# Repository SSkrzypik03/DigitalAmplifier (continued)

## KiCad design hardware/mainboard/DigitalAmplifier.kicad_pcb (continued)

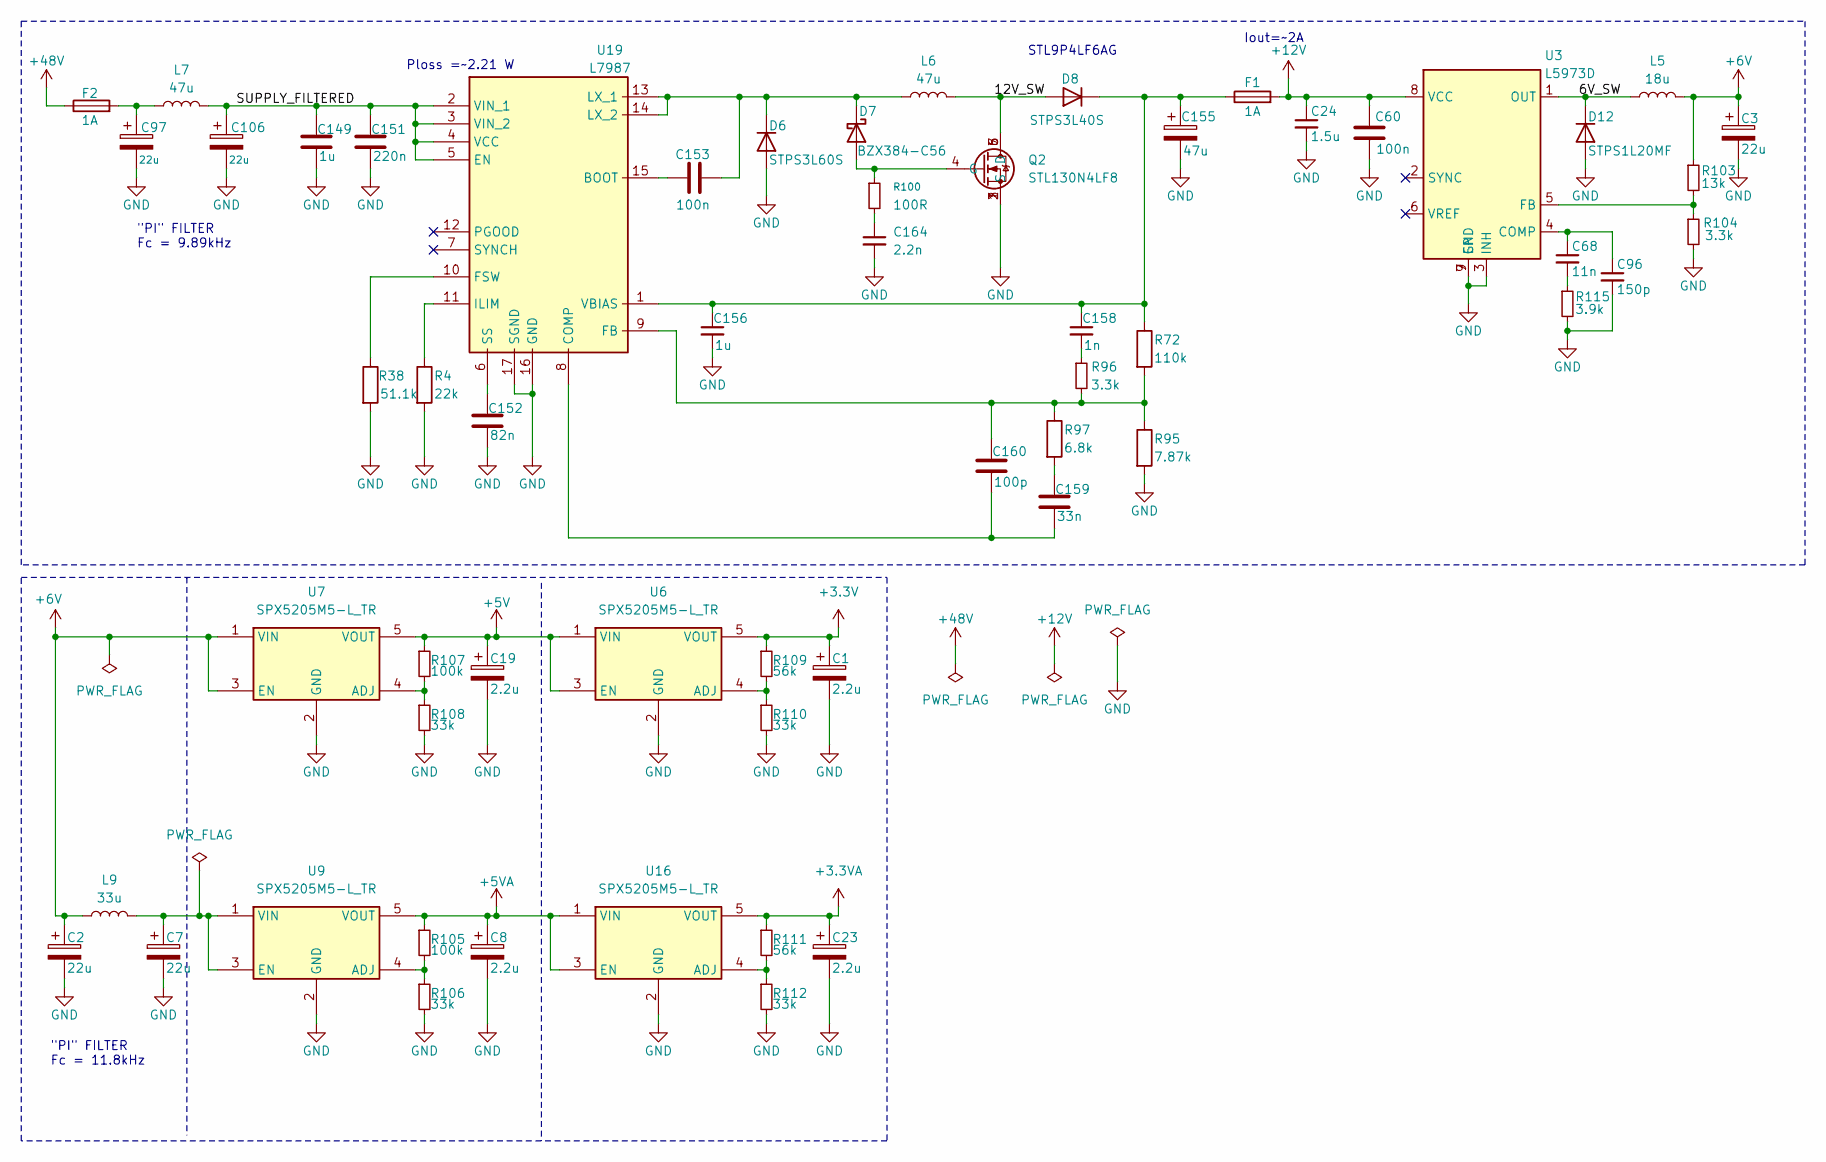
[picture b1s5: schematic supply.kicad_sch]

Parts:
C1, C8, C19, C23: 2.2u; CAPPM3216X180N; Manufacturer_Part_Number 293D225X9016A2TE3
C2, C3, C7: 22u; CAPPM3216X180N; Manufacturer_Part_Number 293D226X9010A2TE3
C24: 1.5u; C_0603_1608Metric; Manufacturer_Part_Number GRM155Z71A225KE01D
C60, C153: 100n; C_0603_1608Metric; Manufacturer_Part_Number 0603B104K500CT
C68: 11n; C_0603_1608Metric; Manufacturer_Part_Number GRM155Z71A225KE01D
C96: 150p; C_0603_1608Metric; Manufacturer_Part_Number GRM155Z71A225KE01D
C97, C106: 22u; CP_Radial_D4.0mm_P2.00mm; Manufacturer_Part_Number ECA1JHG220
C149, C156: 1u; C_0603_1608Metric; Manufacturer_Part_Number CL10A105KB8NNNC
C151: 220n; C_0603_1608Metric; Manufacturer_Part_Number CL10B224KO8NNNC
C152: 82n; C_0603_1608Metric; Manufacturer_Part_Number C0603C823K5RACTU
C155: 47u; CAPPM7343X310N; Manufacturer_Part_Number 293D476X9025D2TE3
C158: 1n; C_0603_1608Metric; Manufacturer_Part_Number 0603B102K500CT
C159: 33n; C_0603_1608Metric; Manufacturer_Part_Number CC0603JRX7R9BB333
C160: 100p; C_0603_1608Metric; Manufacturer_Part_Number CL10C101JB8NNNC
C164: 2.2n; C_0603_1608Metric; Manufacturer_Part_Number GRM1885C1H222JA01D
D6: STPS3L60S; D_SMC; Manufacturer_Part_Number STPS3L60S
D7: BZX384-C56; D_SOD-323; Manufacturer_Part_Number BZX384-C56
D8: STPS3L40S; D_SMC; Manufacturer_Part_Number STPS3L40S
D12: STPS1L20MF; Manufacturer_Part_Number STPS1L20MF
F1, F2: 1A; 0154001.DRT; Manufacturer_Part_Number 0154001.DRT
L5: 18u; L_Wurth_WE-PD2-1054; Manufacturer_Part_Number 744776118
L6: 47u; INDPM120120X1020N; Manufacturer_Part_Number MSS1210-473MED
L7: 47u; INDPM8180X540N; Manufacturer_Part_Number HCM1A0805V2-470-R
L9: 33u; WE-LQ_L49; Manufacturer_Part_Number 744045330
Q2: STL130N4LF8; STL9P4LF6AG; Manufacturer_Part_Number STL130N4LF8
R4: 22k; R_0603_1608Metric; Manufacturer_Part_Number WR06X2202FTL
R38: 51.1k; R_0603_1608Metric; Manufacturer_Part_Number ERJ3EKF5112V
R72: 110k; R_0603_1608Metric; Manufacturer_Part_Number ERJ3GEYJ114V
R95: 7.87k; R_0603_1608Metric; Manufacturer_Part_Number ERJ3EKF7871V
R96, R104: 3.3k; R_0603_1608Metric; Manufacturer_Part_Number ERA-2ARC2612X
R97: 6.8k; R_0603_1608Metric; Manufacturer_Part_Number RC0603FR-076K8L
R100: 100R; R_0603_1608Metric; Manufacturer_Part_Number WR06X1000FTL
R103: 13k; R_0603_1608Metric; Manufacturer_Part_Number RC0402BR-07220KL
R105, R107: 100k; R_0603_1608Metric; Manufacturer_Part_Number CRCW0402100KFKED
R106, R108, R110, R112: 33k; R_0603_1608Metric; Manufacturer_Part_Number ERA2AEB333X
R109, R111: 56k; R_0603_1608Metric; Manufacturer_Part_Number CR0402-FX-5602GLF
R115: 3.9k; R_0603_1608Metric; Manufacturer_Part_Number RC0402BR-07220KL
U3: L5973D; HSOP-8-1EP_3.9x4.9mm_P1.27mm_EP2.41x3.1mm_ThermalVias; Manufacturer_Part_Number L5973D013TR
U6, U7, U9, U16: SPX5205M5-L_TR; SOT95P280X145-5N; Mouser Part Number 701-SPX5205M5-L/TR
U19: L7987; SOP65P640X120-17N; Manufacturer_Part_Number L7987

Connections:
+3.3V: C1.1, R109.1, U6.5 (VOUT); also elsewhere on the board
+3.3VA: C23.1, R111.1, U16.5 (VOUT); also elsewhere on the board
+5V: C19.1, R107.1, U6.1 (VIN), U6.3 (EN), U7.5 (VOUT); also elsewhere on the board
+5VA: C8.1, R105.1, U9.5 (VOUT), U16.1 (VIN), U16.3 (EN); also elsewhere on the board
+6V: C2.1, C3.1, L5.2, L9.1, R103.1, U7.1 (VIN), U7.3 (EN)
+12V: C24.1, C60.2, F1.2, U3.8 (VCC); also elsewhere on the board
+48V: F2.1; also elsewhere on the board
/Supply/6V_SW: D12.2 (K), D12.3 (K), L5.1, U3.1 (OUT)
/Supply/12V_SW: D8.2 (A), L6.2, Q2.5 (D), Q2.6 (D), Q2.7 (D)
/Supply/SUPPLY_FILTERED: C106.1, C149.1, C151.1, L7.2, U19.2 (VIN_1), U19.3 (VIN_2), U19.4 (VCC), U19.5 (EN)
GND: C1.2, C2.2, C3.2, C7.2, C8.2, C19.2, C23.2, C24.2, C60.1, C96.2, C97.2, C106.2, C149.2, C151.2, C152.2, C155.2, C156.2, C164.2, D6.2 (A), D12.1 (A), Q2.1 (S), Q2.2 (S), Q2.3 (S), R4.2, R38.2, R95.2, R104.2, R106.2, R108.2, R110.2, R112.2, R115.2, U3.3 (INH), U3.7 (GND), U3.9 (EP), U6.2 (GND), U7.2 (GND), U9.2 (GND), U16.2 (GND), U19.16 (GND), U19.17 (SGND); also elsewhere on the board
unnamed: C68.2, R115.1
unnamed: C97.1, F2.2, L7.1
unnamed: C158.2, R96.1
unnamed: C159.1, R97.2
unnamed: C164.1, R100.2
unnamed: C153.2, D6.1 (K), D7.1 (K), L6.1, U19.13 (LX_1), U19.14 (LX_2)
unnamed: D7.2 (A), Q2.4 (G), R100.1
unnamed: C155.1, C156.1, C158.1, D8.1 (K), F1.1, R72.1, U19.1 (VBIAS)
unnamed: C68.1, C96.1, U3.4 (COMP)
unnamed: R103.2, R104.1, U3.5 (FB)
unnamed: R109.2, R110.1, U6.4 (ADJ)
unnamed: R107.2, R108.1, U7.4 (ADJ)
unnamed: R105.2, R106.1, U9.4 (ADJ)
unnamed: C7.1, L9.2, U9.1 (VIN), U9.3 (EN)
unnamed: R111.2, R112.1, U16.4 (ADJ)
unnamed: C153.1, U19.15 (BOOT)
unnamed: C159.2, C160.2, U19.8 (COMP)
unnamed: C160.1, R72.2, R95.1, R96.2, R97.1, U19.9 (FB)
unnamed: R38.1, U19.10 (FSW)
unnamed: R4.1, U19.11 (ILIM)
unnamed: C152.1, U19.6 (SS)

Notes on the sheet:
"PI" FILTER Fc = 11.8kHz
"PI" FILTER Fc = 9.89kHz
Iout=~2A
STL9P4LF6AG
Ploss =~2.21 W

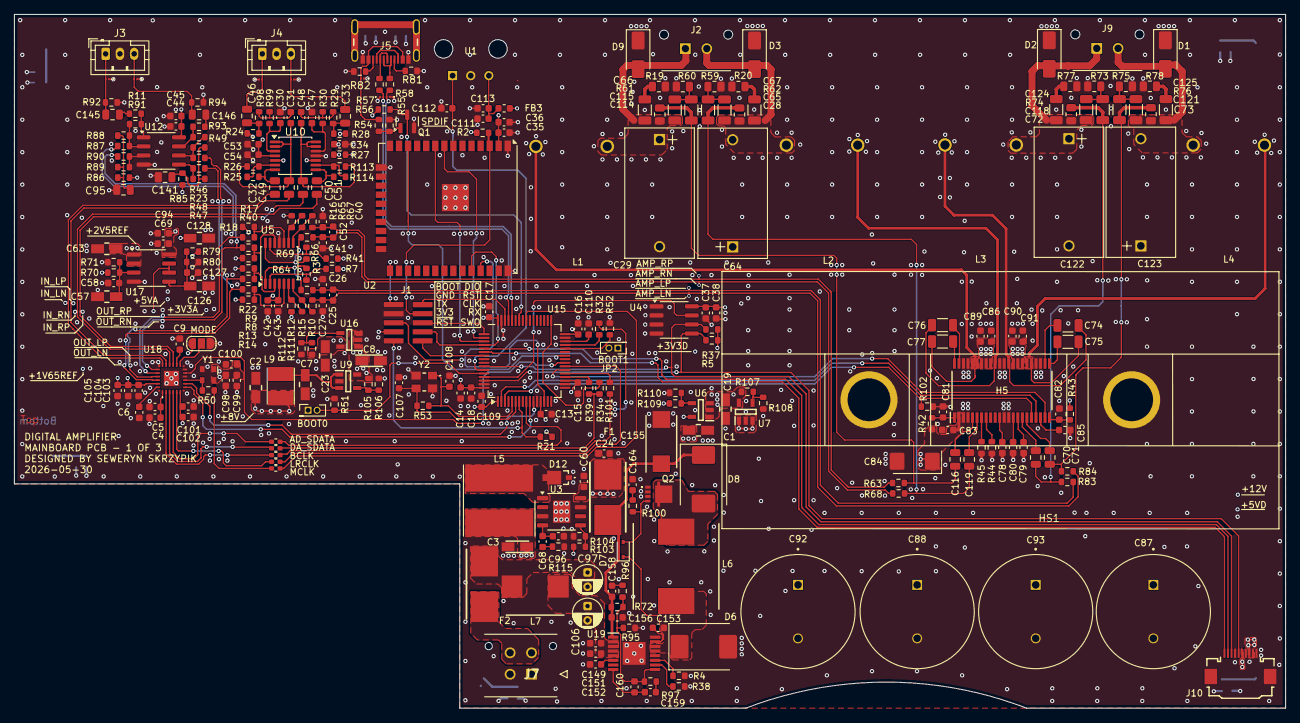
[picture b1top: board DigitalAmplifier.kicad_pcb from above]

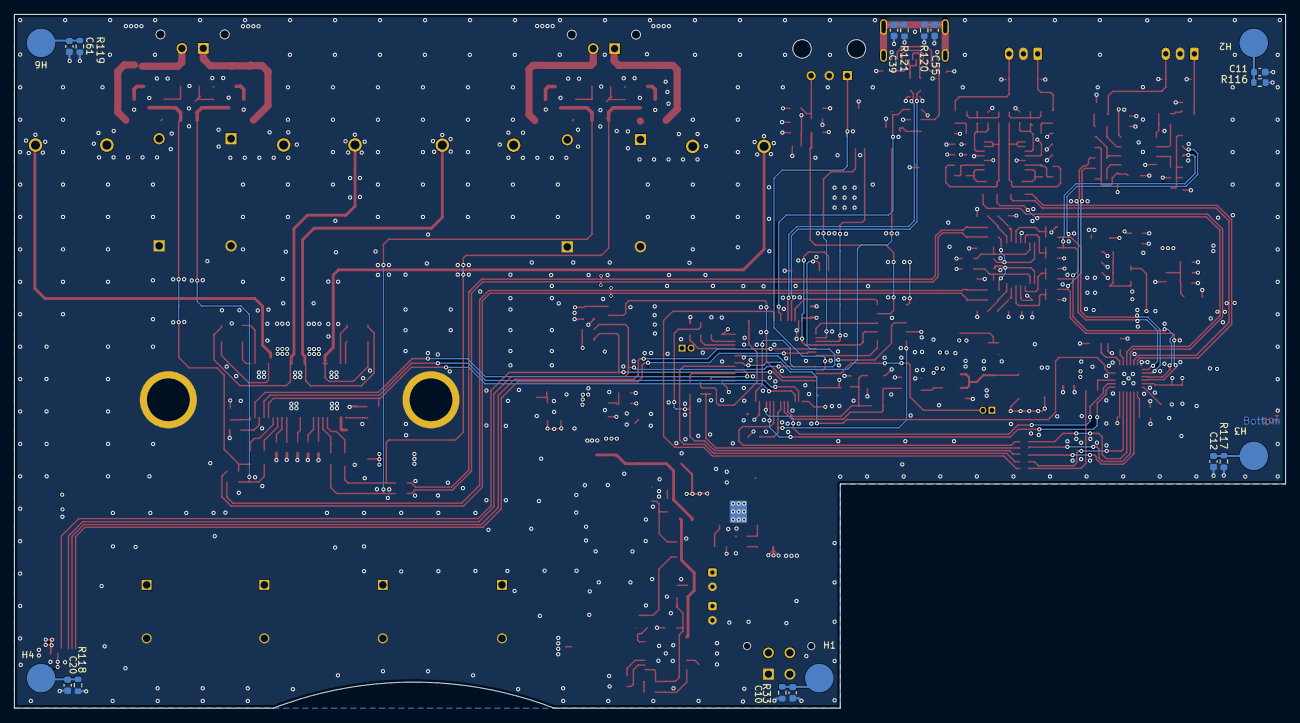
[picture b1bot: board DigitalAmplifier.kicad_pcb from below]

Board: 6 copper layers, 178.1 x 97.2 mm, 318 parts (19 on the bottom side), 187 nets.

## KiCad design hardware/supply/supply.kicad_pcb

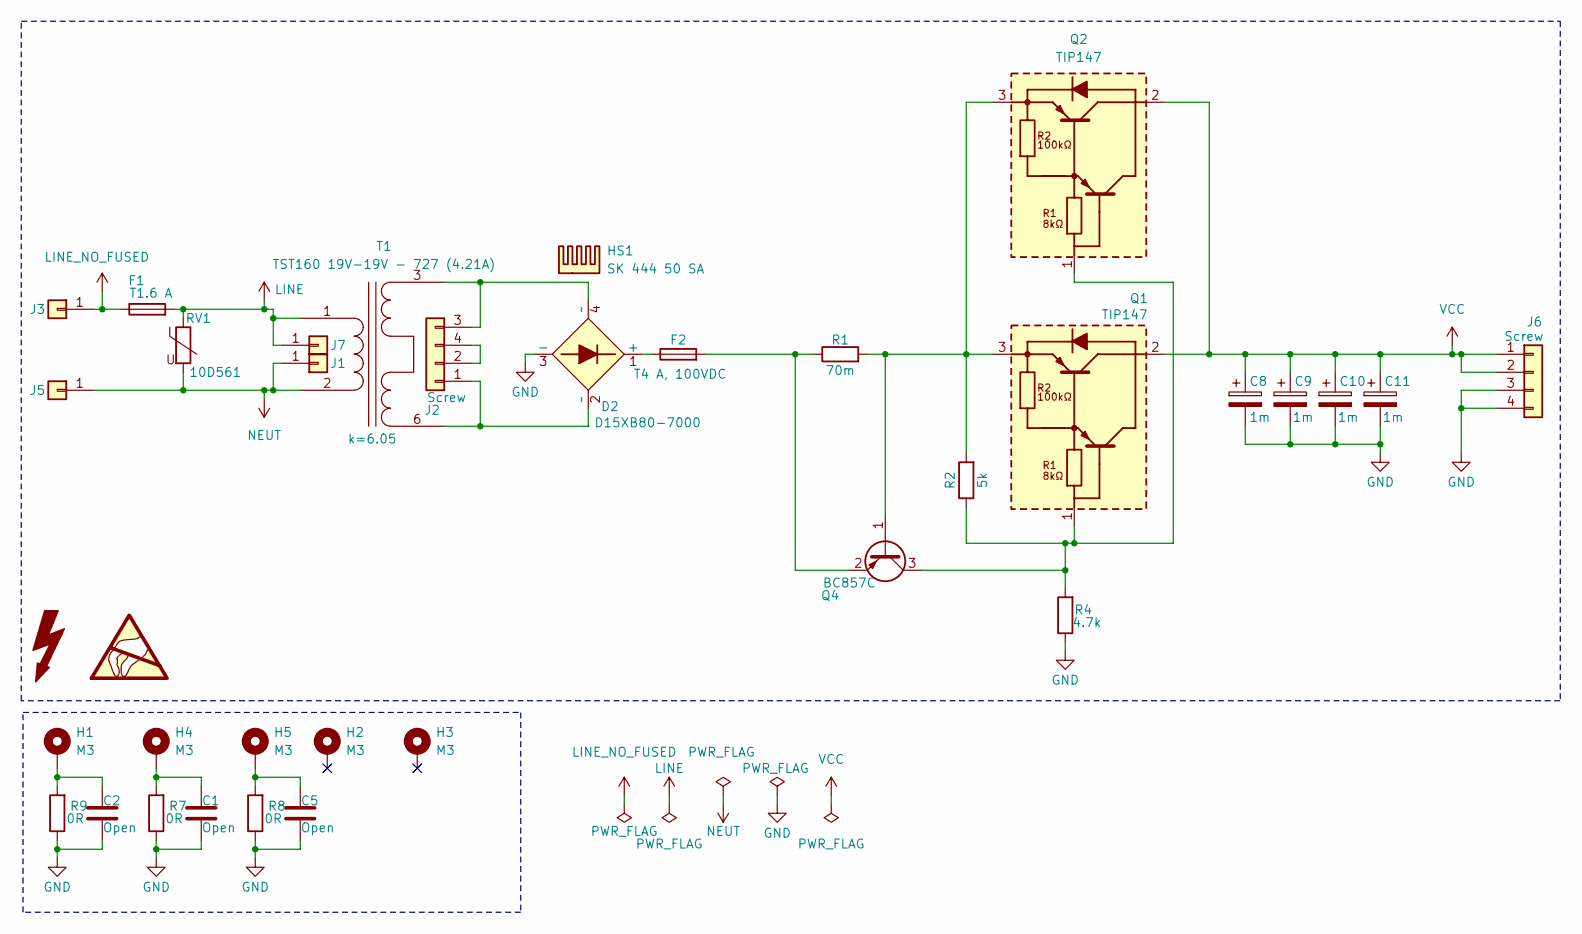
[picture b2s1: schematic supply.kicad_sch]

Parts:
C1, C2, C5: Open; C_0603_1608Metric
C8, C9, C10, C11: 1m; CP_Radial_D30.0mm_P10.00mm_SnapIn; Manufacturer_Part_Number HJ1J109M30050HC
D2: D15XB80-7000; D25XB1007000; Manufacturer_Part_Number D15XB80-7000
F1: T1.6 A; Fuseholder_Cylinder-5x20mm_Schurter_0031_8201_Horizontal_Op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; Manufacturer_Part_Number 0031.8201
F2: T4 A, 100VDC; FUSE_0154004.DRT; Manufacturer_Part_Number 0154004.DRT
H1, H2, H3, H4, H5: M3; WA-SMSI_97730256330; Manufacturer_Part_Number 9775056360R
HS1: SK 444 50 SA; Manufacturer_Part_Number SK_444 5_SA
J1, J3, J5, J7: Conn_01x01; 726386-2; Manufacturer_Part_Number 726386-2
J2, J6: Screw; 43045-04YY_121314; Manufacturer_Part_Number 43045-04YY_121314
Q1, Q2: TIP147; TO545P515X1560X2445-3P; Manufacturer_Part_Number TIP147
Q4: BC857C; SOT-23; Manufacturer_Part_Number BC857C
R1: 70m; Manufacturer_Part_Number TLRP3A30CR070FTE
R2: 5k; R_0805_2012Metric; Manufacturer_Part_Number RC0603FR-074K7L
R4: 4.7k; R_0805_2012Metric; Manufacturer_Part_Number RC0603FR-074K7L
R7, R8, R9: 0R; R_0603_1608Metric; Manufacturer_Part_Number CRCW06030000Z0EA
RV1: 10D561; MOV-14D_5.2MM-T_; Manufacturer_Part_Number 10D561
T1: TST160 19V-19V - 727 (4.21A)

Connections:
GND: C1.2, C2.2, C5.2, C8.2, C9.2, C10.2, C11.2, D2.3 (-), J6.3, J6.4, R4.1, R7.1, R8.1, R9.1
LINE: F1.2, J7.1 (Pin_1_1), RV1.1, T1.1 (AA)
LINE_NO_FUSED: F1.1, J3.1 (Pin_1_1)
NEUT: J1.1 (Pin_1_1), J5.1 (Pin_1_1), RV1.2, T1.2 (AB)
unnamed: C1.1, H4.1 (1_1), R7.2
unnamed: C2.1, H1.1 (1_1), R9.2
unnamed: C5.1, H5.1 (1_1), R8.2
unnamed: D2.1 (+), F2.1
unnamed: D2.2 (~~), J2.1, T1.6 (SD)
unnamed: J2.2, J2.4
unnamed: D2.4 (~~), J2.3, T1.3 (SA)
unnamed: Q1.1 (B), Q2.1 (B), Q4.3 (C), R2.1, R4.2
unnamed: Q1.3 (E), Q2.3 (E), Q4.1 (B), R1.2, R2.2
unnamed: F2.2, Q4.2 (E), R1.1
VCC: C8.1, C9.1, C10.1, C11.1, J6.1, J6.2, Q1.2 (C), Q2.2 (C)

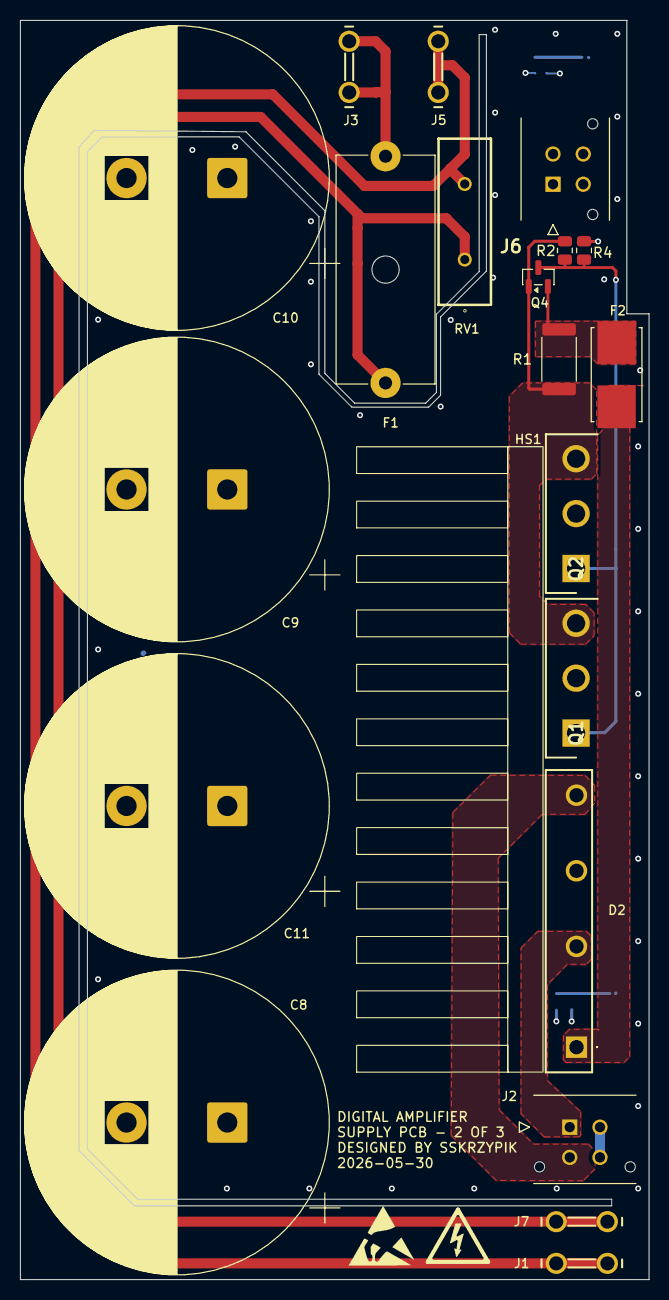
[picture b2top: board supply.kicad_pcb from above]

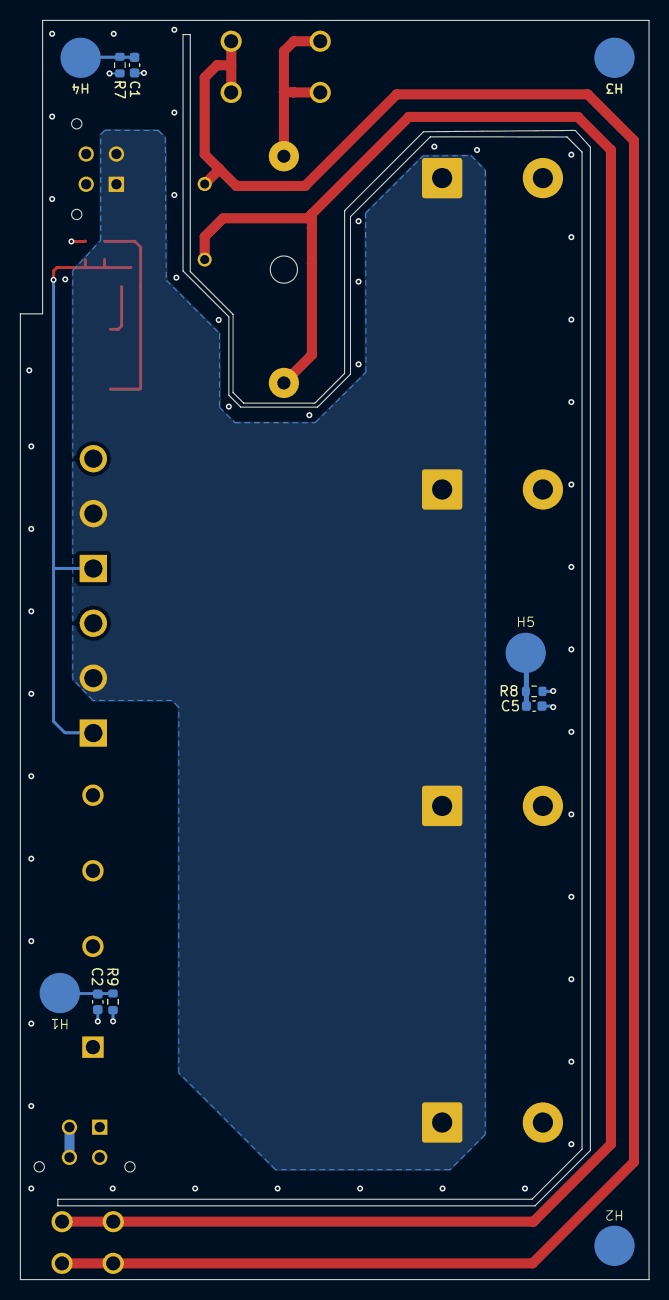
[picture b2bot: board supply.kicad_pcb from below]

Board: 4 copper layers, 62.4 x 125.0 mm, 32 parts (11 on the bottom side), 15 nets.

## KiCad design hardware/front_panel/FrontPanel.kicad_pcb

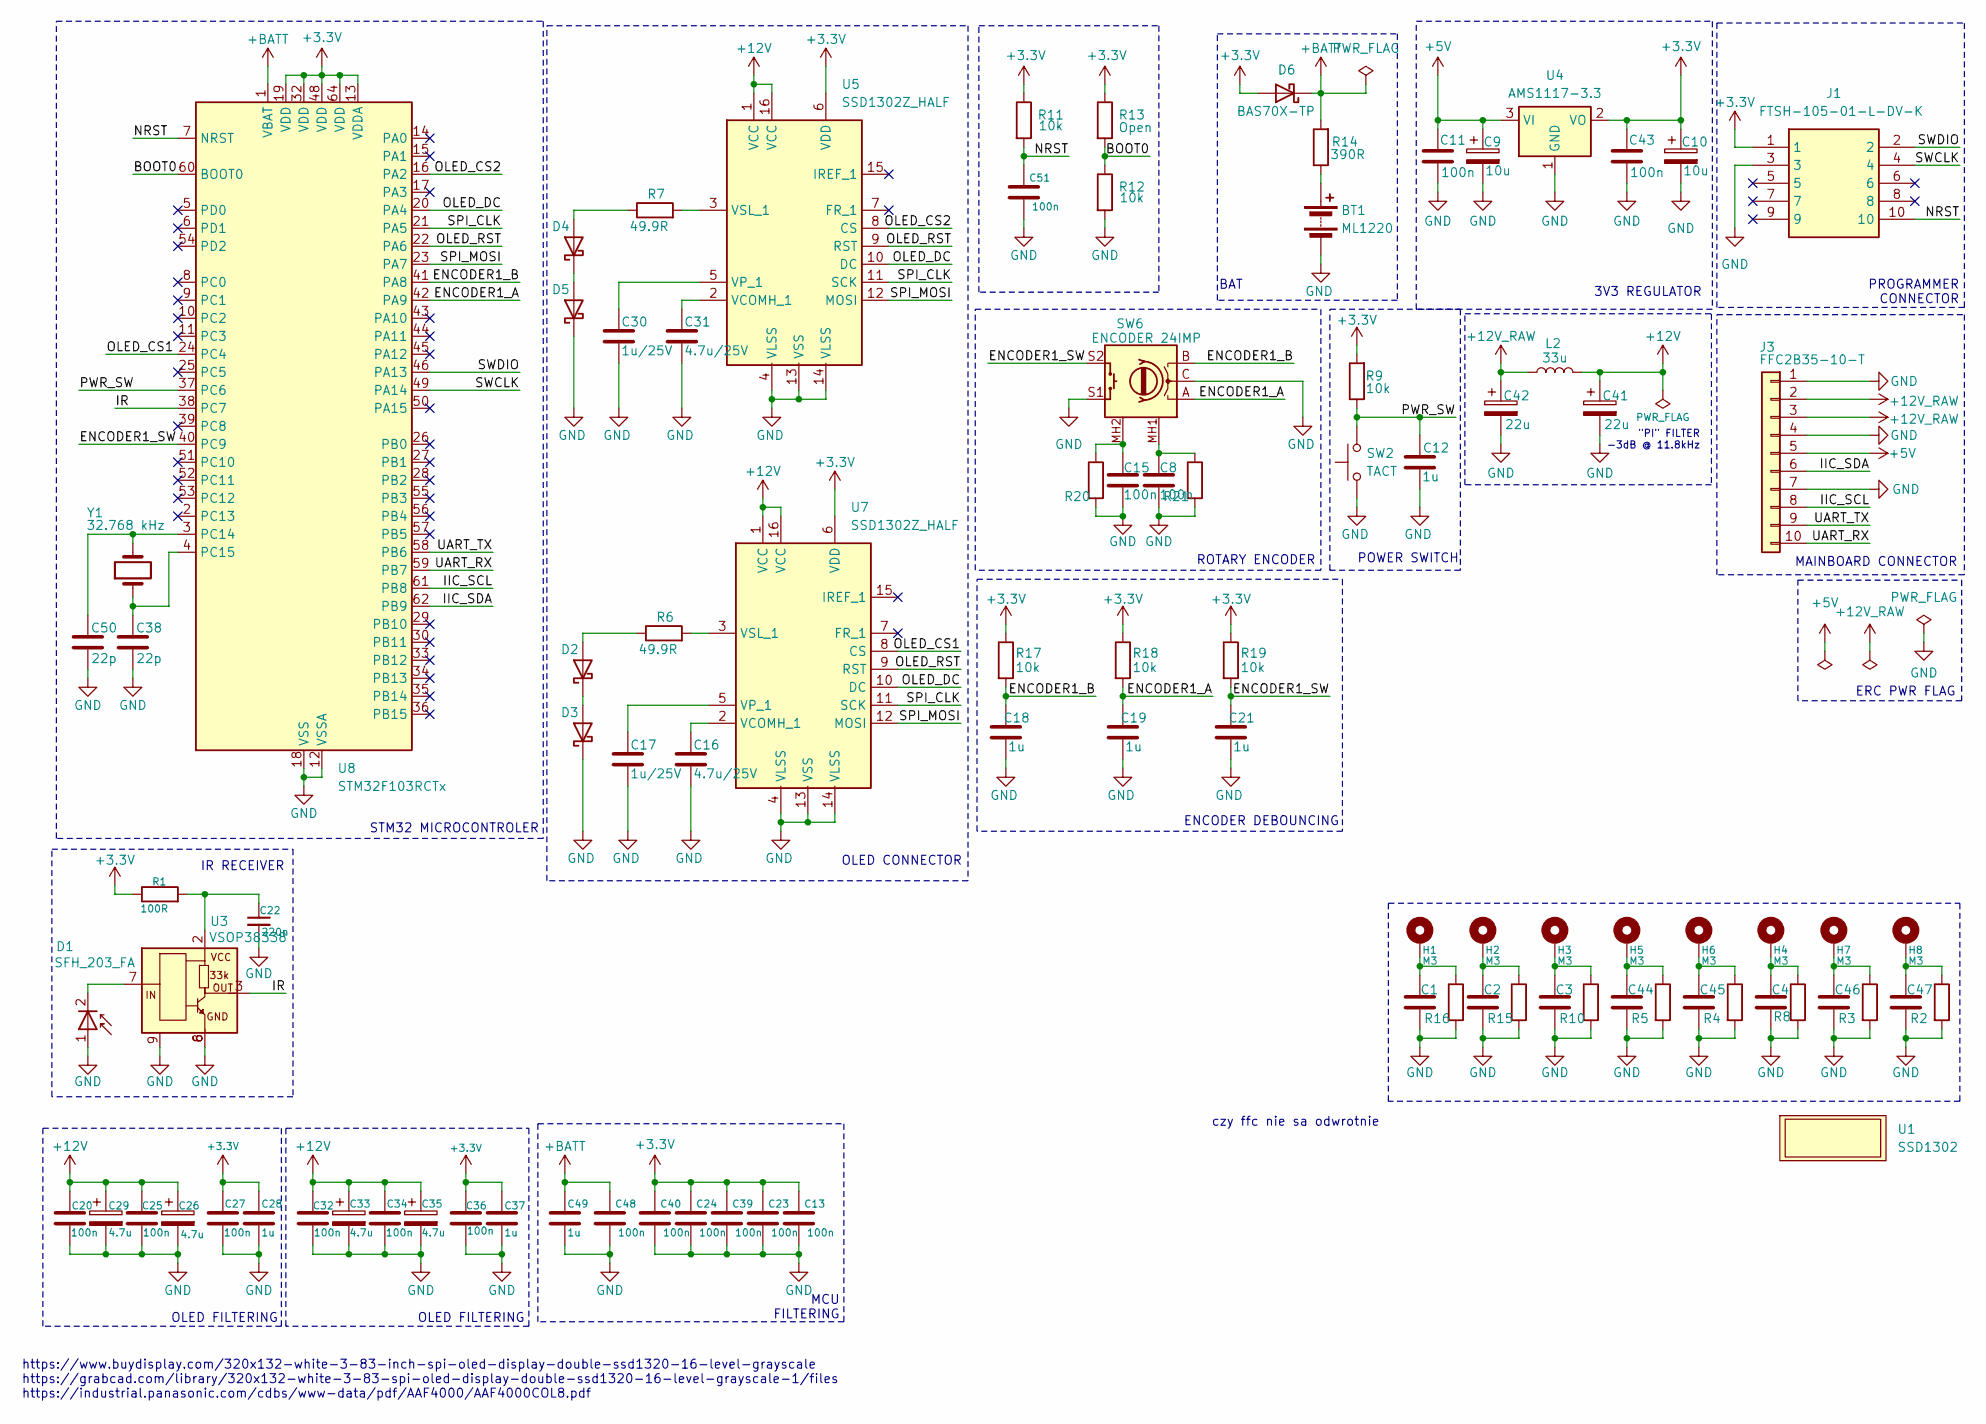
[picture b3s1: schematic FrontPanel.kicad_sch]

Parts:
BT1: ML1220; BatteryHolder_LINX_BAT-HLD-012-SMT
C1, C2, C3, C4, C8, C11, C13, C15, C20, C23, C24, C25, C27, C32, C34, C36, C39, C40, C43, C44, C45, C46, C47, C48, C51: 100n; C_0603_1608Metric
C9, C10: 10u; CAPPM3216X180N
C12, C18, C19, C21, C28, C37, C49: 1u; C_0603_1608Metric
C16, C31: 4.7u/25V; C_0603_1608Metric
C17, C30: 1u/25V; C_0603_1608Metric
C22: 220n; C_0603_1608Metric
C26, C29, C33, C35: 4.7u; CAPPM3528X210N; Manufacturer_Part_Number 293D475X9016B2TE3
C38, C50: 22p; C_0603_1608Metric
C41, C42: 22u; CAPPM3216X180N; Manufacturer_Part_Number 293D226X9010A2TE3
D1: SFH_203_FA; SFH203FA; Manufacturer_Part_Number SFH 203 FA
D2, D3, D4, D5: RB500VM-40TE-17; D_SOD-323F; Manufacturer_Part_Number RB500VM-40TE-17
D6: BAS70X-TP; D_SOD-523; Manufacturer_Part_Number BAS70X-TP
H1, H2, H3, H4, H5, H6, H7, H8: M3; MountingHole_3.2mm_M3_Pad_Via
J1: FTSH-105-01-L-DV-K; FTSH10501LDVK; Manufacturer_Part_Number FTSH-105-01-L-DV-K
J3: FFC2B35-10-T; FFC2B3510T
L2: 33u; WE-LQ_L49; Manufacturer_Part_Number WE-LQ_L49
R1: 100R; R_0603_1608Metric
R2, R3, R4, R5, R8, R10, R15, R16, R20, R21: 1M; R_0603_1608Metric
R6, R7: 49.9R; R_0603_1608Metric
R9, R11, R12, R17, R18, R19: 10k; R_0603_1608Metric
R13: Open; R_0603_1608Metric
R14: 390R; R_0603_1608Metric
SW2: TACT; SW_SPST_PTS645Sx43SMTR92
SW6: ENCODER 24IMP; PEC11R4220FS0024; Manufacturer_Part_Number PEC11R-4220F-S0024
U1: SSD1302
U3: VSOP38338; SON50P200X200X81-9N-D; Mouser Part Number 782-VSOP38338
U4: AMS1117-3.3; SOT-223-3_TabPin2
U5, U7: SSD1302Z_HALF; 527461671; Manufacturer_Part_Number 52746-1671
U8: STM32F103RCTx; LQFP-64_10x10mm_P0.5mm
Y1: 32.768 kHz; QT3CD32768KDZYT; Manufacturer_Part_Number QT3CD-32.768KDZY-T

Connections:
+3.3V: C10.1, C13.1, C23.1, C24.1, C27.1, C28.1, C36.1, C37.1, C39.1, C40.1, C43.1, D6.2 (A), J1.1, R1.1, R9.2, R11.1, R13.1, R17.1, R18.1, R19.1, U4.2 (VO), U5.6 (VDD), U7.6 (VDD), U8.13 (VDDA), U8.19 (VDD), U8.32 (VDD), U8.48 (VDD), U8.64 (VDD)
+5V: C9.1, C11.1, J3.5, U4.3 (VI)
+12V: C20.1, C25.1, C26.1, C29.1, C32.1, C33.1, C34.1, C35.1, C41.1, L2.2, U5.1 (VCC), U5.16 (VCC), U7.1 (VCC), U7.16 (VCC)
+12V_RAW: C42.1, J3.2, J3.3, L2.1
+BATT: C48.1, C49.1, D6.1 (K), R14.2, U8.1 (VBAT)
/BOOT0: R12.1, R13.2, U8.60 (BOOT0)
/ENCODER1_A: C19.1, R18.2, SW6.A, U8.42 (PA9)
/ENCODER1_B: C18.1, R17.2, SW6.B, U8.41 (PA8)
/ENCODER1_SW: C21.1, R19.2, SW6.S2, U8.40 (PC9)
/IIC_SCL: J3.8, U8.61 (PB8)
/IIC_SDA: J3.6, U8.62 (PB9)
/IR: U3.3 (OUT), U8.38 (PC7)
/NRST: C51.1, J1.10, R11.2, U8.7 (NRST)
/OLED_CS1: U7.8 (CS), U8.24 (PC4)
/OLED_CS2: U5.8 (CS), U8.16 (PA2)
/OLED_DC: U5.10 (DC), U7.10 (DC), U8.20 (PA4)
/OLED_RST: U5.9 (RST), U7.9 (RST), U8.22 (PA6)
/PWR_SW: C12.1, R9.1, SW2.2, U8.37 (PC6)
/SPI_CLK: U5.11 (SCK), U7.11 (SCK), U8.21 (PA5)
/SPI_MOSI: U5.12 (MOSI), U7.12 (MOSI), U8.23 (PA7)
/SWCLK: J1.4, U8.49 (PA14)
/SWDIO: J1.2, U8.46 (PA13)
/UART_RX: J3.10, U8.59 (PB7)
/UART_TX: J3.9, U8.58 (PB6)
GND: BT1.2 (-), C1.2, C2.2, C3.2, C4.2, C8.2, C9.2, C10.2, C11.2, C12.2, C13.2, C15.2, C16.2, C17.2, C18.2, C19.2, C20.2, C21.2, C22.2, C23.2, C24.2, C25.2, C26.2, C27.2, C28.2, C29.2, C30.2, C31.2, C32.2, C33.2, C34.2, C35.2, C36.2, C37.2, C38.2, C39.2, C40.2, C41.2, C42.2, C43.2, C44.2, C45.2, C46.2, C47.2, C48.2, C49.2, C50.2, C51.2, D1.1 (A), D3.1 (K), D5.1 (K), J1.3, J3.1, J3.4, J3.7, R2.2, R3.2, R4.2, R5.2, R8.2, R10.2, R12.2, R15.2, R16.2, R20.2, R21.2, SW2.1, SW6.C, SW6.S1, U3.6 (GND), U3.8 (GND), U3.9 (EP), U4.1 (GND), U5.4 (VLSS), U5.13 (VSS), U5.14 (VLSS), U7.4 (VLSS), U7.13 (VSS), U7.14 (VLSS), U8.12 (VSSA), U8.18 (VSS), U8.31 (VSS), U8.47 (VSS), U8.63 (VSS)
unnamed: BT1.1 (+), R14.1
unnamed: C1.1, H1.1 (1_1), R16.1
unnamed: C2.1, H2.1 (1_1), R15.1
unnamed: C3.1, H3.1 (1_1), R10.1
unnamed: C4.1, H4.1 (1_1), R8.1
unnamed: C8.1, R21.1, SW6.MH1
unnamed: C15.1, R20.1, SW6.MH2
unnamed: C44.1, H5.1 (1_1), R5.1
unnamed: C45.1, H6.1 (1_1), R4.1
unnamed: C46.1, H7.1 (1_1), R3.1
unnamed: C47.1, H8.1 (1_1), R2.1
unnamed: D1.2 (K), U3.7 (IN)
unnamed: D2.2 (A), R6.1
unnamed: D2.1 (K), D3.2 (A)
unnamed: D4.2 (A), R7.1
unnamed: D4.1 (K), D5.2 (A)
unnamed: C22.1, R1.2, U3.2 (VCC)
unnamed: C31.1, U5.2 (VCOMH_1)
unnamed: C30.1, U5.5 (VP_1)
unnamed: R7.2, U5.3 (VSL_1)
unnamed: C16.1, U7.2 (VCOMH_1)
unnamed: C17.1, U7.5 (VP_1)
unnamed: R6.2, U7.3 (VSL_1)
unnamed: C50.1, U8.3 (PC14), Y1.2
unnamed: C38.1, U8.4 (PC15), Y1.1

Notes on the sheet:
https://www.buydisplay.com/320x132-white-3-83-inch-spi-oled-display-double-ssd1320-16-level-grayscale https://grabcad.com/library/320x132-white-3-83-spi-oled-display-double-ssd1320-16-level-grayscale-1/files https://industrial.panasonic.com/cdbs/www-data/pdf/AAF4000/AAF4000COL8.pdf
ROTARY ENCODER
czy ffc nie sa odwrotnie
OLED CONNECTOR
MAINBOARD CONNECTOR
IR RECEIVER
ENCODER DEBOUNCING
"PI" FILTER -3dB @ 11.8kHz
POWER SWITCH
STM32 MICROCONTROLER
OLED FILTERING
PROGRAMMER CONNECTOR
MCU FILTERING
ERC PWR FLAG
BAT
3V3 REGULATOR

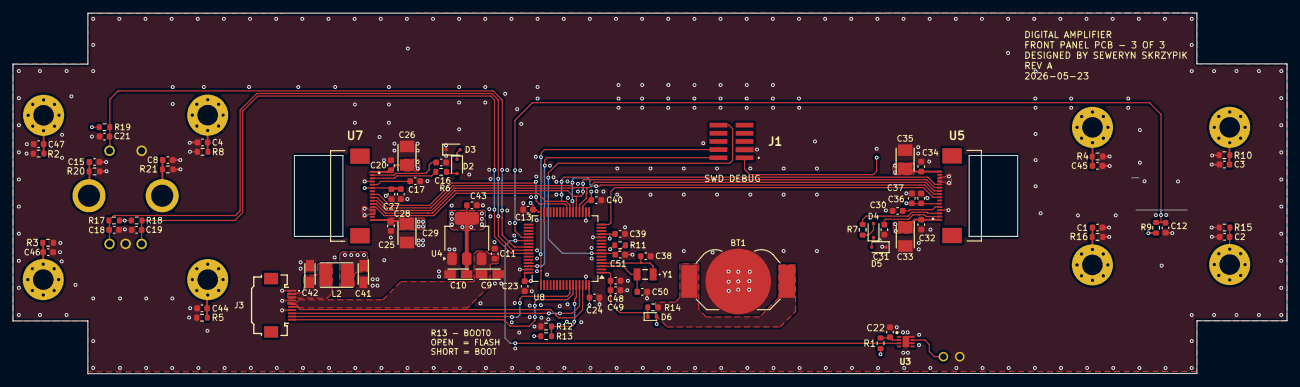
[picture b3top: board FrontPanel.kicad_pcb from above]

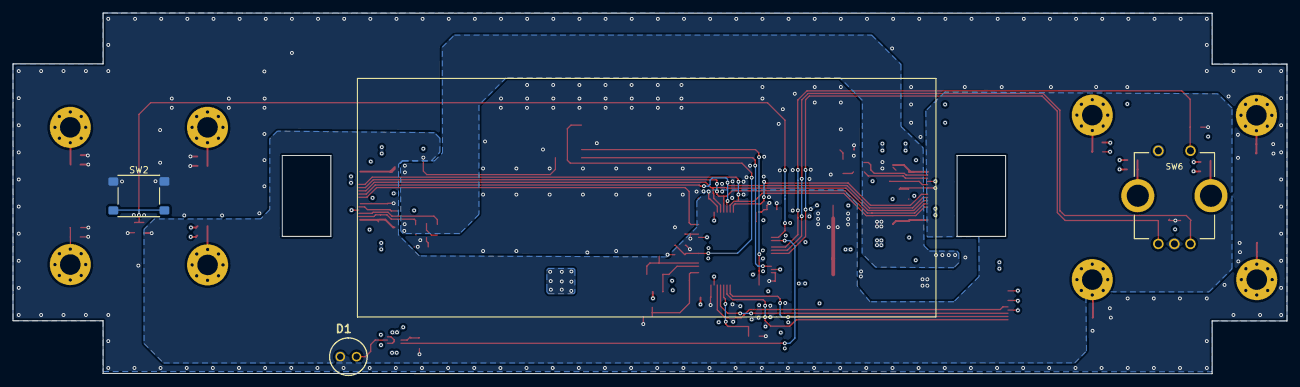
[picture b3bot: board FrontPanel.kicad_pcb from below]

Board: 4 copper layers, 198.4 x 56.2 mm, 94 parts (3 on the bottom side), 50 nets.

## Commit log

2026-05-24 Add power supply and front panel PCBs
2026-05-24 Add power supply simulation files
2026-05-24 docs: add project and PCB images
2026-05-26 replace mosfets with bjts in inrush current limiter
2026-05-26 swap power connectors and flip front panel PCB orientation
2026-06-01 Prepare PCB for production
2026-06-03 docs update
2026-06-03 Add enclosure CAD models
2026-06-05 added new images
2026-06-05 improved logo
